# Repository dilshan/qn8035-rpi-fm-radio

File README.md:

# QN8035 based Raspberry Pi FM radio receiver.

[QN8035](https://datasheetspdf.com/pdf-down/Q/N/8/QN8035_Quintic.pdf) is a single-chip stereo FM radio receiver IC designed by the *Quintic Corporation*. This receiver supports the FM broadcast band ranging from 60MHz to 108MHz. 

This repository contains a *[Raspberry Pi](https://www.raspberrypi.org/products/raspberry-pi-3-model-b/)* base QN8035 receiver to receive FM stereo broadcasts from 88MHz to 108MHz.

The hardware part of this receiver consists of a QN8035 tuner and a 32.768kHz oscillator circuit. These circuits are designed to work with a 3.3V power supply.

The prototype version of this tuner designs with a single-sided PCB. All the schematics and *KiCAD* PCB design files are available in this repository. The Gerber files of this PCB are available to download at the release section of this repository.

The QN8035 uses the I2C bus to communicate with the host system. The tuner application develops with this system utilizes I2C channel 1 (*Raspberry Pi* header Pin 3 and 5) to communicate with the QN8035. The control software presents in this repository is designed to work with the *Raspberry Pi* operating system and is set to run on May 7th, 2021 (*Buster*), or the latest releases.

The tuner application provided in this release supports the following features:

 - Manual and automatic station scanning. 
 - Decode RDS PS (program service) data. 
 - Volume control.
 - Display RSSI and SNR readings receive from the tuner.

The control application of this receiver develops using *GCC* and *[WiringPi](http://wiringpi.com/)* library. 

The complete construction and configuration steps of this tuner show in the video above.

This is an open-source hardware project. All schematics, design files, and PCB layouts have been released under the [Creative Commons Attribution 4.0 International](https://creativecommons.org/licenses/by/4.0/) license. The control software is released under the terms of the [MIT License](https://opensource.org/licenses/MIT).

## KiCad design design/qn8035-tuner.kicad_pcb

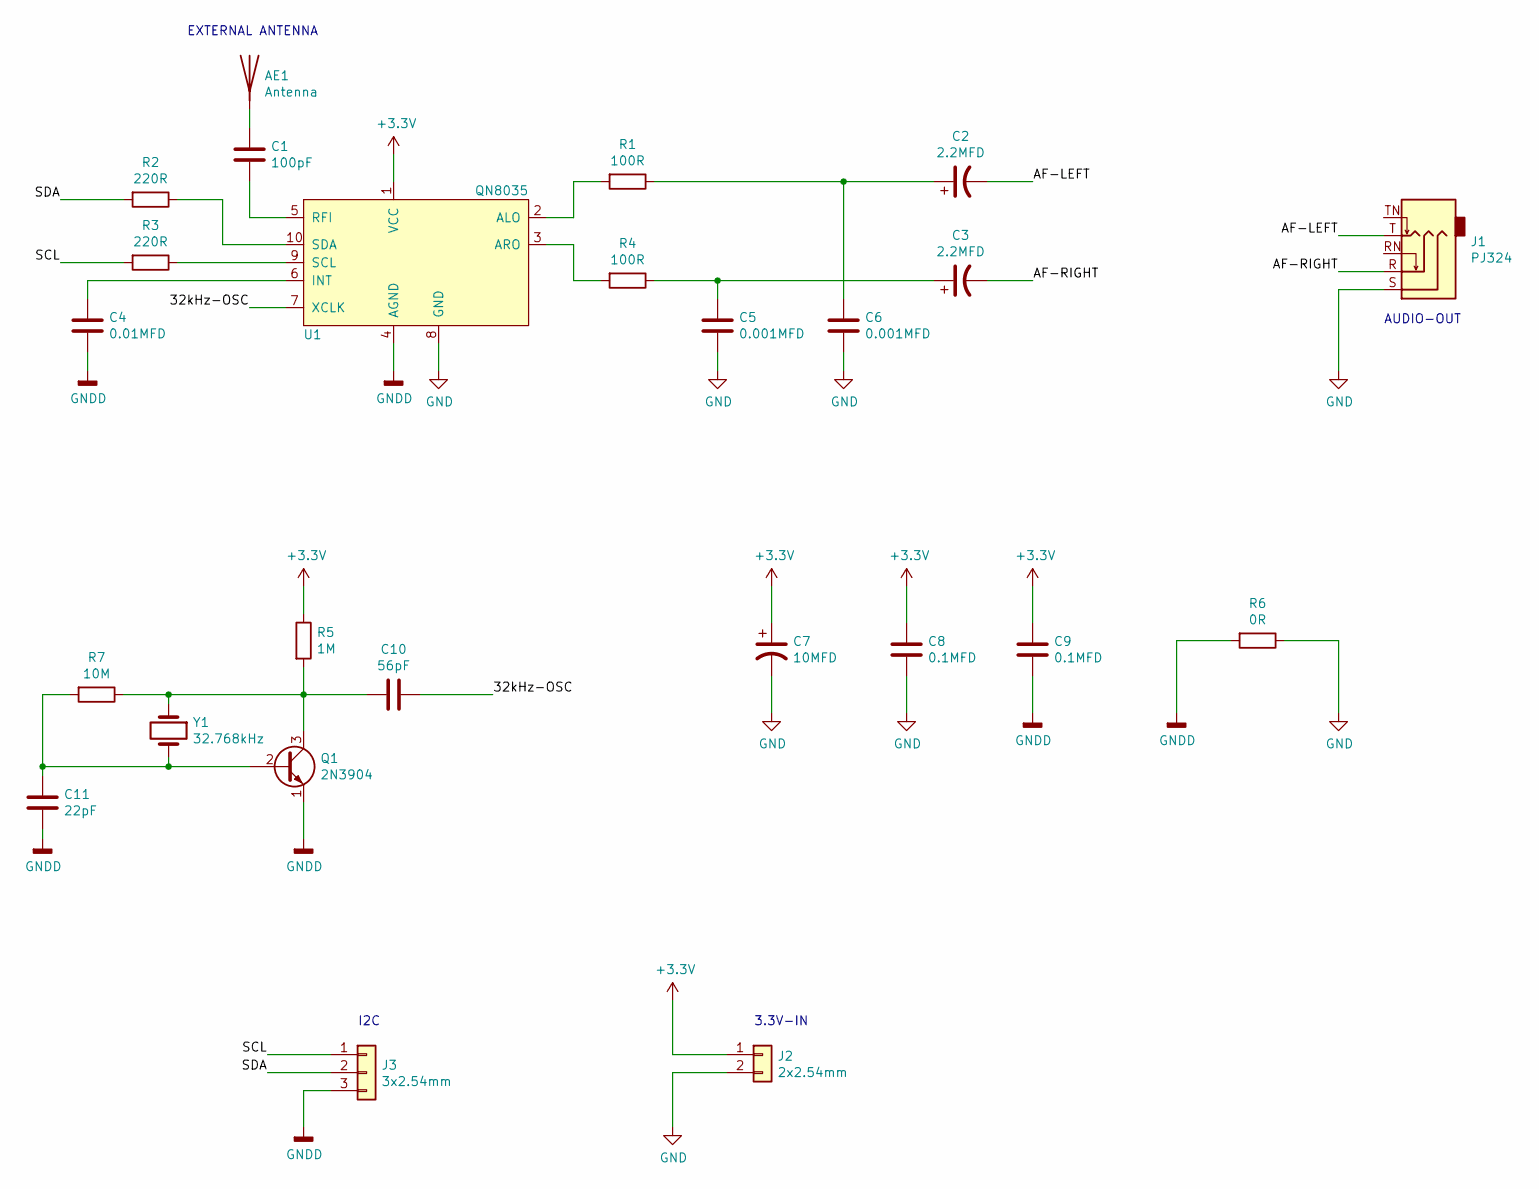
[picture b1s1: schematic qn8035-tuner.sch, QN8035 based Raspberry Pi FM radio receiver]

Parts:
AE1: Antenna; TestPoint_Loop_D2.50mm_Drill1.0mm
C1: 100pF; C_Disc_D3.0mm_W2.0mm_P2.50mm
C2, C3: 2.2MFD; CP_Radial_D5.0mm_P2.50mm
C4: 0.01MFD; C_Disc_D5.0mm_W2.5mm_P5.00mm
C5, C6: 0.001MFD; C_Disc_D5.0mm_W2.5mm_P5.00mm
C7: 10MFD; CP_Radial_D5.0mm_P2.50mm
C8, C9: 0.1MFD; C_Disc_D6.0mm_W2.5mm_P5.00mm
C10: 56pF; C_Disc_D5.1mm_W3.2mm_P5.00mm
C11: 22pF; C_Disc_D3.0mm_W1.6mm_P2.50mm
J1: PJ324; Jack_3.5mm_Ledino_KB3SPRS_Horizontal
J2: 2x2.54mm; PinHeader_1x02_P2.54mm_Vertical
J3: 3x2.54mm; PinHeader_1x03_P2.54mm_Vertical
Q1: 2N3904; TO-92_HandSolder
R1, R4: 100R; R_Axial_DIN0204_L3.6mm_D1.6mm_P7.62mm_Horizontal
R2, R3: 220R; R_Axial_DIN0204_L3.6mm_D1.6mm_P7.62mm_Horizontal
R5: 1M; R_Axial_DIN0204_L3.6mm_D1.6mm_P7.62mm_Horizontal
R6: 0R; R_0805_2012Metric_Pad1.20x1.40mm_HandSolder
R7: 10M; R_Axial_DIN0204_L3.6mm_D1.6mm_P7.62mm_Horizontal
U1: QN8035; DIP-10_W7.62mm_LongPads
Y1: 32.768kHz; Crystal_AT310_D3.0mm_L10.0mm_Vertical

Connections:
+3V3: C7.1, C8.1, C9.1, J2.1, R5.1, U1.1 (VCC)
/32kHz-OSC: C10.1, U1.7 (XCLK)
/AF-LEFT: C2.2, J1.T
/AF-RIGHT: C3.2, J1.R
/SCL: J3.1, R3.2
/SDA: J3.2, R2.2
GND: C5.2, C6.2, C7.2, C8.2, J1.S, J2.2, R6.1, U1.8 (GND)
GNDD: C4.2, C9.2, C11.1, J3.3, Q1.1 (E), R6.2, U1.4 (AGND)
unnamed: AE1.1, C1.1
unnamed: C1.2, U1.5 (RFI)
unnamed: C2.1, C6.1, R1.1
unnamed: C3.1, C5.1, R4.1
unnamed: C4.1, U1.6 (INT)
unnamed: C10.2, Q1.3 (C), R5.2, R7.1, Y1.1
unnamed: C11.2, Q1.2 (B), R7.2, Y1.2
unnamed: R1.2, U1.2 (ALO)
unnamed: R2.1, U1.10 (SDA)
unnamed: R3.1, U1.9 (SCL)
unnamed: R4.2, U1.3 (ARO)

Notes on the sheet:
AUDIO-OUT
EXTERNAL ANTENNA
I2C
3.3V-IN

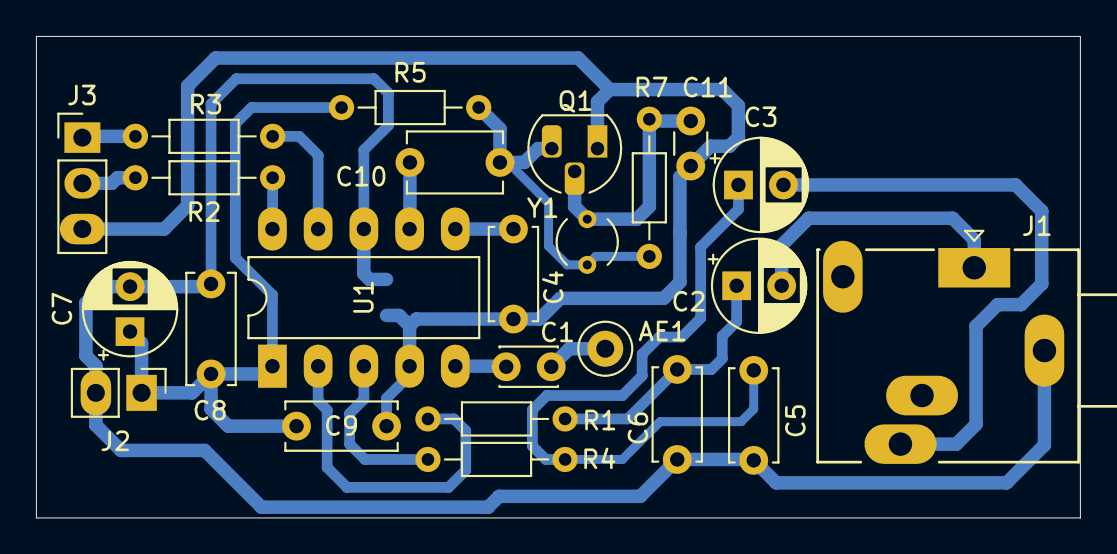
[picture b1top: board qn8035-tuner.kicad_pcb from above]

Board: 2 copper layers, 58.0 x 26.8 mm, 25 parts (1 on the bottom side), 19 nets.

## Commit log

2021-09-02 Initial version of QN8035 test console for RPi3.
2021-09-02 Remove debug lines from the QN8035 scanning routines.
2021-09-04 Add initial version of readme file.
2021-09-04 Add MIT license.
2021-09-04 Add KiCAD design files and schematics.
2021-09-04 Add fritzing design and support resources.
2021-09-05 Add initial version of BOM file.
2021-09-05 Add Raspberry Pi3 connection diagrams.
2021-09-05 Update BOM file with package details.
2021-09-05 Minor edit in readme.md file.
2021-09-06 Add connection diagrams in PDF format.
2021-09-06 Link connection diagram into the readme.md file.
2021-09-06 Add Video preview image.
2021-09-06 Add video preview image and link to the readme.md file.

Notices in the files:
design/qn8035-tuner.kicad_pcb:
Released under the Creative Commons Attribution 4.0 International license
